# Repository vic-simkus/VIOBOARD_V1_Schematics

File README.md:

# VIOBOARD_V1_Schematics
Schematics for VIOBOAD Version 1.0

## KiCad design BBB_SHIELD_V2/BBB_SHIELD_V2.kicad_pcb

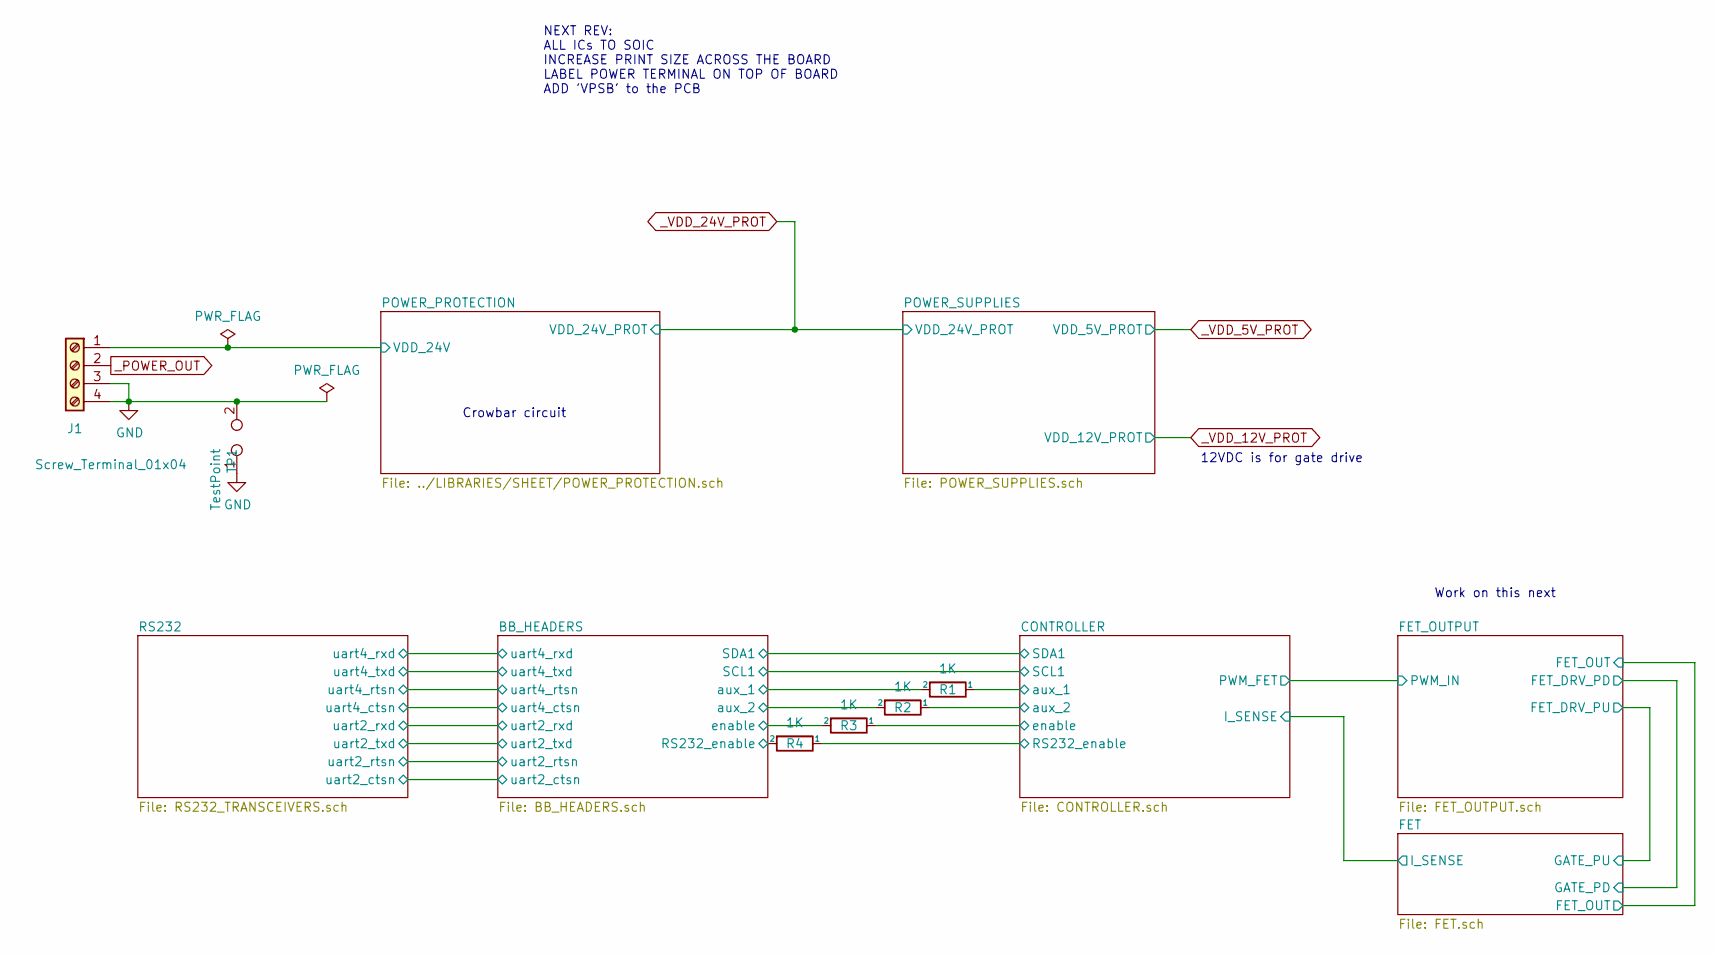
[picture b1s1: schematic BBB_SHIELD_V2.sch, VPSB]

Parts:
J1: Screw_Terminal_01x04; OSTTA044163
R1, R2, R3, R4: 1K; R_0805_2012Metric; MFGPN CRCW08051K00FKEAC
TP1: TestPoint; PinHeader_1x02_P1.27mm_Vertical

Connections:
/BB_HEADERS/RS232_enable: R4.2; also elsewhere on the board
/BB_HEADERS/aux_1: R1.2; also elsewhere on the board
/BB_HEADERS/aux_2: R2.2; also elsewhere on the board
/BB_HEADERS/enable: R3.2; also elsewhere on the board
/CONTROLLER/RS232_enable: R4.1; also elsewhere on the board
/CONTROLLER/aux_1: R1.1; also elsewhere on the board
/CONTROLLER/aux_2: R2.1; also elsewhere on the board
/CONTROLLER/enable: R3.1; also elsewhere on the board
/POWER_PROTECTION/VDD_24V: J1.1; also elsewhere on the board
GND: J1.3, J1.4, TP1.1, TP1.2; also elsewhere on the board
_POWER_OUT: J1.2; also elsewhere on the board

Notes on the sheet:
NEXT REV: ALL ICs TO SOIC INCREASE PRINT SIZE ACROSS THE BOARD LABEL POWER TERMINAL ON TOP OF BOARD ADD 'VPSB' to the PCB
12VDC is for gate drive
Crowbar circuit
Work on this next

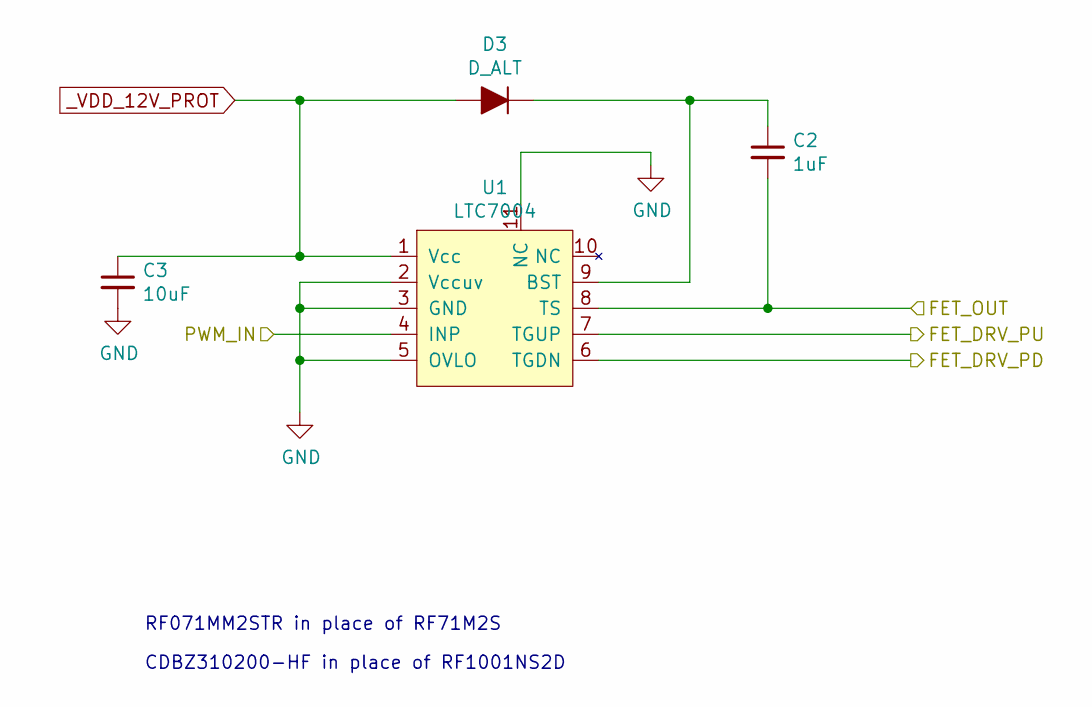
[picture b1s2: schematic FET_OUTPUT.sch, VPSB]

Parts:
C2: 1uF; C_0805_2012Metric; VOLTAGE 50; MFGPN CL21B104KBCNNNC
C3: 10uF; C_1206_3216Metric; VOLTAGE 50; MFGPN CL31B106KBHNNNE
D3: D_ALT; D_SOD-123F; MFGPN RF071MM2STR
U1: LTC7004; MSOP-10; MFGPN LTC7004IMSE#PBF

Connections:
/CONTROLLER/PWM_FET: U1.4 (INP); also elsewhere on the board
/FET/FET_OUT: C2.2, U1.8 (TS); also elsewhere on the board
/FET_OUTPUT/FET_DRV_PD: U1.6 (TGDN); also elsewhere on the board
/FET_OUTPUT/FET_DRV_PU: U1.7 (TGUP); also elsewhere on the board
GND: C3.2, U1.2 (Vccuv), U1.3 (GND), U1.5 (OVLO), U1.11 (NC); also elsewhere on the board
unnamed: C2.1, D3.1 (K), U1.9 (BST)
_VDD_12V_PROT: C3.1, D3.2 (A), U1.1 (Vcc); also elsewhere on the board

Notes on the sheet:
‎RF071MM2STR‎ in place of RF71M2S
CDBZ310200-HF in place of RF1001NS2D

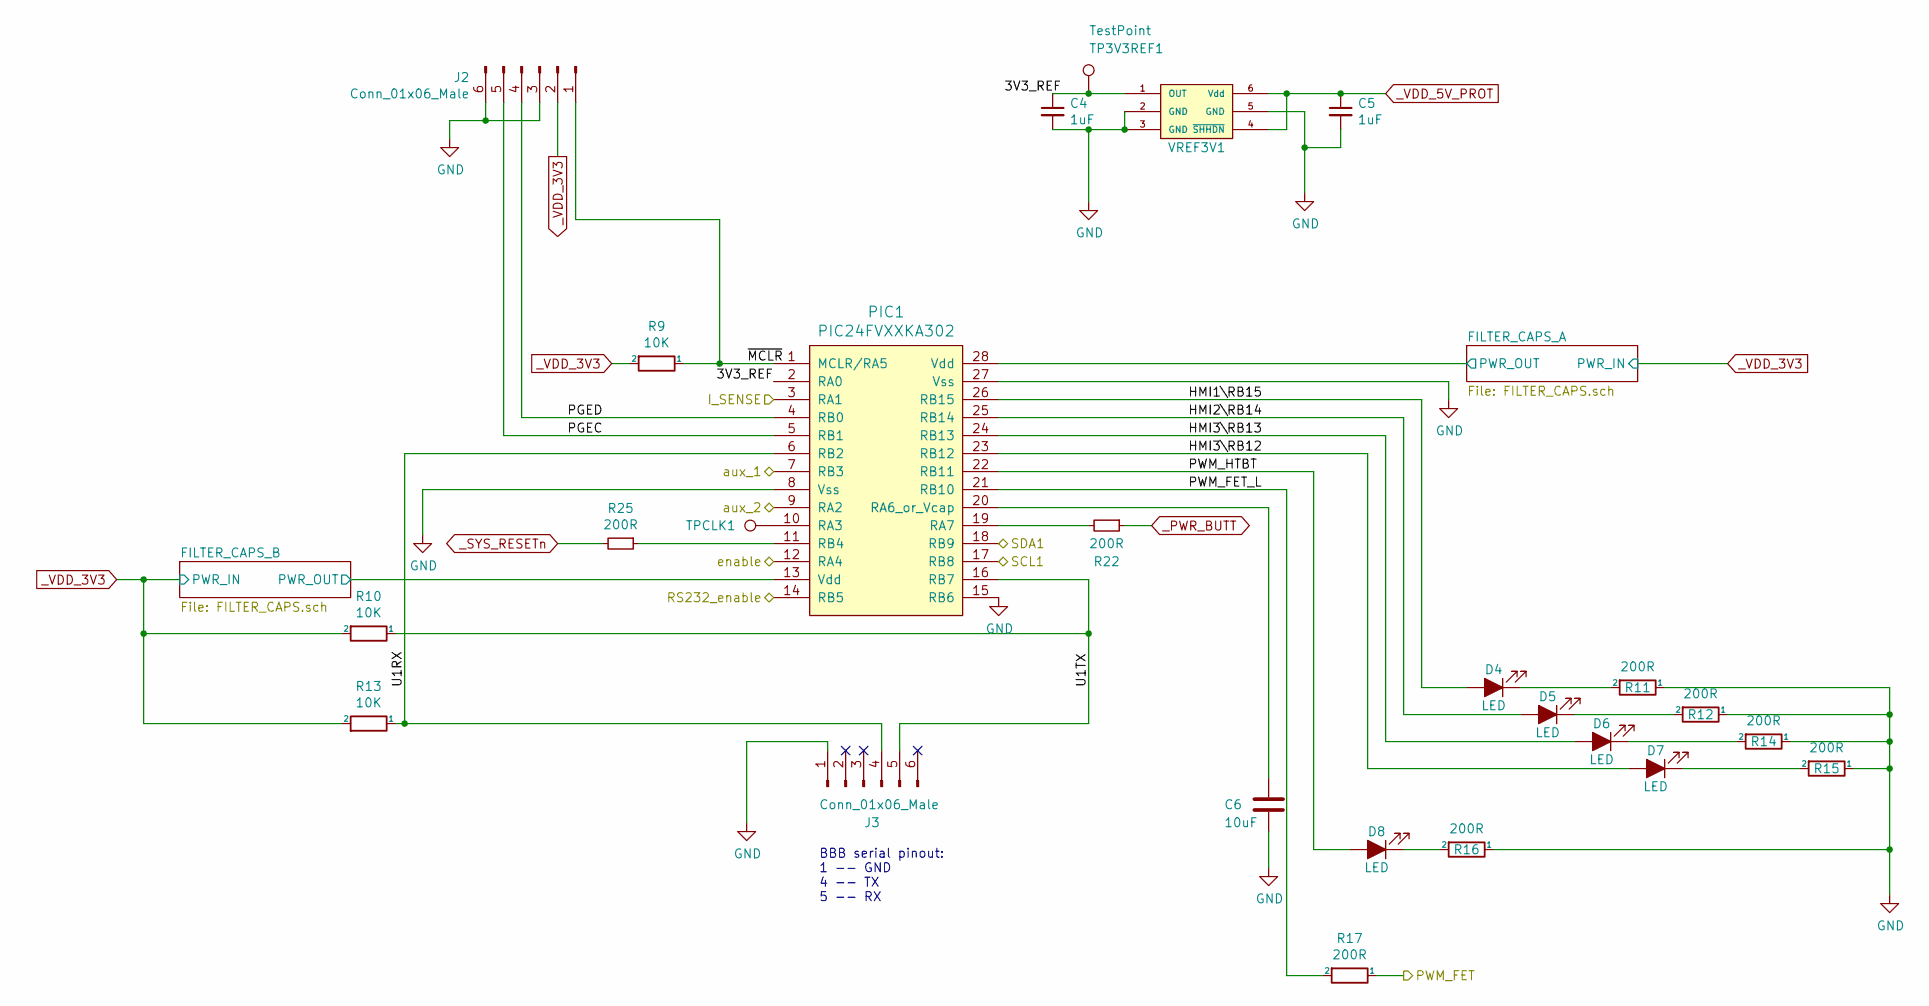
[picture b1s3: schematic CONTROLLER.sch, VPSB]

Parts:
C4, C5: 1uF; C_0805_2012Metric; VOLTAGE 50; MFGPN CL21B105KBFNFNE
C6: 10uF; C_0805_2012Metric; VOLTAGE 10; MFGPN CL21A106KPFNNNE
D4, D5, D6, D7, D8: LED; LED_0805_2012Metric_Castellated; VOLTAGE NA
J2, J3: Conn_01x06_Male; PinHeader_1x06_P2.54mm_Horizontal; MFGPN 0022052061
PIC1: PIC24FVXXKA302; SOIC-28W_7.5x17.9mm_P1.27mm; MFGPN PIC24FV32KA302-I/SO
R9, R10, R13: 10K; R_0805_2012Metric; MFGPN CRCW080510K0FKTA
R11, R12, R14, R15, R16, R17, R22, R25: 200R; R_0805_2012Metric; MFGPN CRCW0805200RFKEAC
TP3V3REF1: TestPoint; TestPoint_THTPad_D1.0mm_Drill0.5mm
TPCLK1: TestPoint; TestPoint_THTPad_D1.0mm_Drill0.5mm
VREF3V1: MCP1501_SOT-23-6; SOT-23-6; MFGPN MCP1501T-33E/CHY

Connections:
/BB_HEADERS/SCL1: PIC1.17 (RB8); also elsewhere on the board
/BB_HEADERS/SDA1: PIC1.18 (RB9); also elsewhere on the board
/CONTROLLER/3V3_REF: C4.1, PIC1.2 (RA0), TP3V3REF1.1, VREF3V1.1 (OUT)
/CONTROLLER/HMI1\RB15: D4.2 (A), PIC1.26 (RB15)
/CONTROLLER/HMI2\RB14: D5.2 (A), PIC1.25 (RB14)
/CONTROLLER/HMI3\RB12: D7.2 (A), PIC1.23 (RB12)
/CONTROLLER/HMI3\RB13: D6.2 (A), PIC1.24 (RB13)
/CONTROLLER/I_SENSE: PIC1.3 (RA1); also elsewhere on the board
/CONTROLLER/PGEC: J2.5, PIC1.5 (RB1)
/CONTROLLER/PGED: J2.4, PIC1.4 (RB0)
/CONTROLLER/PWM_FET: R17.1; also elsewhere on the board
/CONTROLLER/PWM_FET_L: PIC1.21 (RB10), R17.2
/CONTROLLER/PWM_HTBT: D8.2 (A), PIC1.22 (RB11)
/CONTROLLER/RS232_enable: PIC1.14 (RB5); also elsewhere on the board
/CONTROLLER/U1RX: J3.4, PIC1.6 (RB2), R13.1
/CONTROLLER/U1TX: J3.5, PIC1.16 (RB7), R10.1
/CONTROLLER/aux_1: PIC1.7 (RB3); also elsewhere on the board
/CONTROLLER/aux_2: PIC1.9 (RA2); also elsewhere on the board
/CONTROLLER/enable: PIC1.12 (RA4); also elsewhere on the board
/CONTROLLER/~MCLR: J2.1, PIC1.1 (MCLR/RA5), R9.1
GND: C4.2, C5.2, C6.2, J2.3, J2.6, J3.1, PIC1.8 (Vss), PIC1.15 (RB6), PIC1.27 (Vss), R11.1, R12.1, R14.1, R15.1, R16.1, VREF3V1.2 (GND), VREF3V1.3 (GND), VREF3V1.5 (GND); also elsewhere on the board
unnamed: C6.1, PIC1.20 (RA6_or_Vcap)
unnamed: D4.1 (K), R11.2
unnamed: D5.1 (K), R12.2
unnamed: D6.1 (K), R14.2
unnamed: D7.1 (K), R15.2
unnamed: D8.1 (K), R16.2
unnamed: PIC1.10 (RA3), TPCLK1.1
unnamed: PIC1.11 (RB4), R25.1
unnamed: PIC1.19 (RA7), R22.2
_PWR_BUTT: R22.1; also elsewhere on the board
_SYS_RESETn: R25.2; also elsewhere on the board
_VDD_3V3: J2.2, PIC1.13 (Vdd), PIC1.28 (Vdd), R9.2, R10.2, R13.2; also elsewhere on the board
_VDD_5V_PROT: C5.1, VREF3V1.4 (~SHHDN), VREF3V1.6 (Vdd); also elsewhere on the board

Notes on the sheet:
BBB serial pinout: 1 -- GND 4 -- TX 5 -- RX

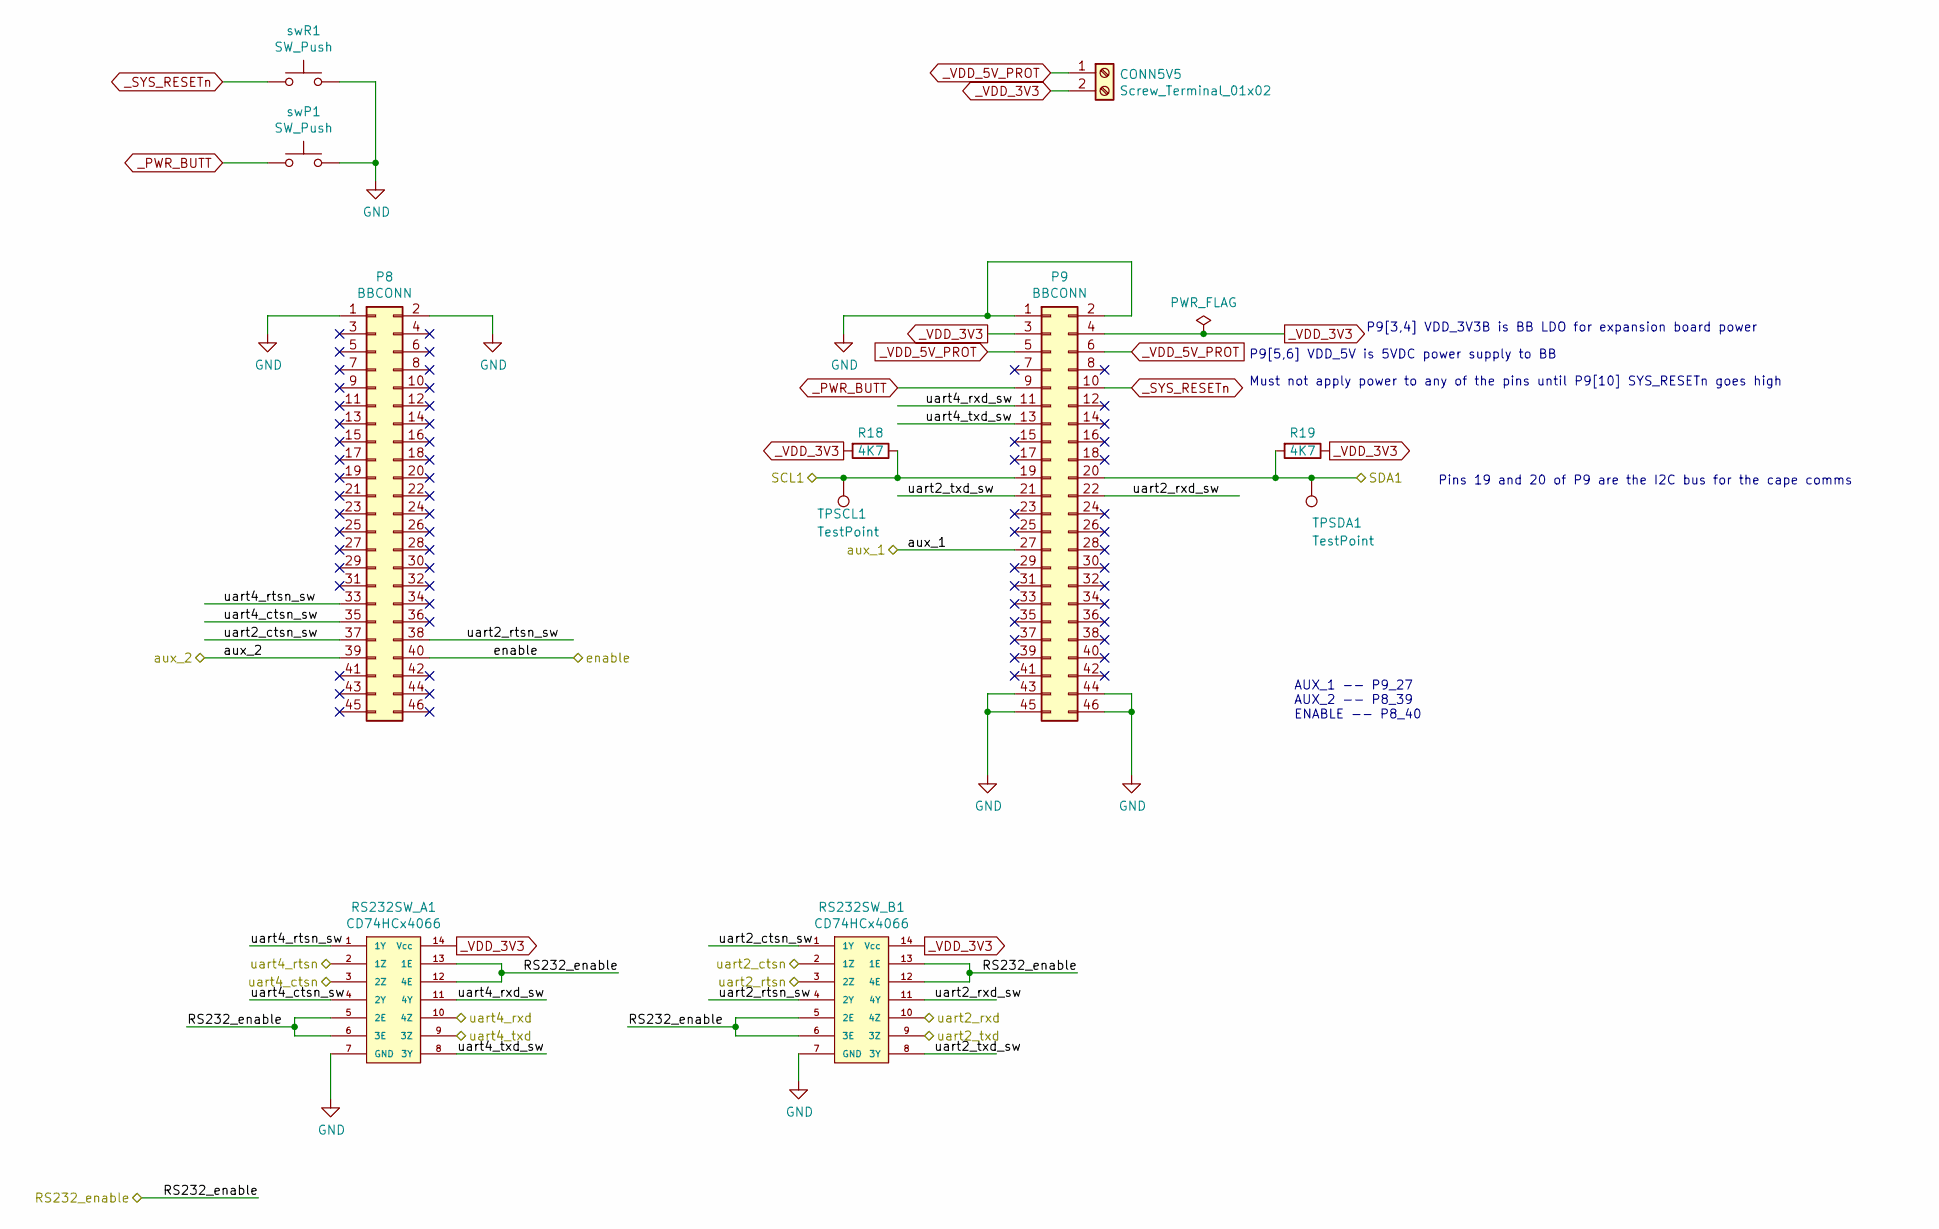
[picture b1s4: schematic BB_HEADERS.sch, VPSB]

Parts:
CONN5V5: Screw_Terminal_01x02; OSTTA024163
P8, P9: BBCONN; PinHeader_2x23_P2.54mm_Vertical
R18, R19: 4K7; R_0805_2012Metric; MFGPN CRCW08054K70FKEAC
RS232SW_A1, RS232SW_B1: CD74HCx4066; SOIC-14_3.9x8.7mm_P1.27mm; MFGPN CD74HC4066M96
TPSCL1: TestPoint; PinHeader_1x01_P1.27mm_Vertical
TPSDA1: TestPoint; PinHeader_1x01_P1.27mm_Vertical
swP1: SW_Push; SW_PUSH_6mm
swR1: SW_Push; SW_PUSH_6mm

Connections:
/BB_HEADERS/RS232_enable: RS232SW_A1.5 (2E), RS232SW_A1.6 (3E), RS232SW_A1.12 (4E), RS232SW_A1.13 (1E), RS232SW_B1.5 (2E), RS232SW_B1.6 (3E), RS232SW_B1.12 (4E), RS232SW_B1.13 (1E); also elsewhere on the board
/BB_HEADERS/SCL1: P9.19, R18.1, TPSCL1.1; also elsewhere on the board
/BB_HEADERS/SDA1: P9.20, R19.2, TPSDA1.1; also elsewhere on the board
/BB_HEADERS/aux_1: P9.27; also elsewhere on the board
/BB_HEADERS/aux_2: P8.39; also elsewhere on the board
/BB_HEADERS/enable: P8.40; also elsewhere on the board
/BB_HEADERS/uart2_ctsn: RS232SW_B1.2 (1Z); also elsewhere on the board
/BB_HEADERS/uart2_ctsn_sw: P8.37, RS232SW_B1.1 (1Y)
/BB_HEADERS/uart2_rtsn: RS232SW_B1.3 (2Z); also elsewhere on the board
/BB_HEADERS/uart2_rtsn_sw: P8.38, RS232SW_B1.4 (2Y)
/BB_HEADERS/uart2_rxd: RS232SW_B1.10 (4Z); also elsewhere on the board
/BB_HEADERS/uart2_rxd_sw: P9.22, RS232SW_B1.11 (4Y)
/BB_HEADERS/uart2_txd: RS232SW_B1.9 (3Z); also elsewhere on the board
/BB_HEADERS/uart2_txd_sw: P9.21, RS232SW_B1.8 (3Y)
/BB_HEADERS/uart4_ctsn: RS232SW_A1.3 (2Z); also elsewhere on the board
/BB_HEADERS/uart4_ctsn_sw: P8.35, RS232SW_A1.4 (2Y)
/BB_HEADERS/uart4_rtsn: RS232SW_A1.2 (1Z); also elsewhere on the board
/BB_HEADERS/uart4_rtsn_sw: P8.33, RS232SW_A1.1 (1Y)
/BB_HEADERS/uart4_rxd: RS232SW_A1.10 (4Z); also elsewhere on the board
/BB_HEADERS/uart4_rxd_sw: P9.11, RS232SW_A1.11 (4Y)
/BB_HEADERS/uart4_txd: RS232SW_A1.9 (3Z); also elsewhere on the board
/BB_HEADERS/uart4_txd_sw: P9.13, RS232SW_A1.8 (3Y)
GND: P8.1, P8.2, P9.1, P9.2, P9.43, P9.44, P9.45, P9.46, RS232SW_A1.7 (GND), RS232SW_B1.7 (GND), swP1.2, swR1.2; also elsewhere on the board
_PWR_BUTT: P9.9, swP1.1; also elsewhere on the board
_SYS_RESETn: P9.10, swR1.1; also elsewhere on the board
_VDD_3V3: CONN5V5.2, P9.3, P9.4, R18.2, R19.1, RS232SW_A1.14 (Vcc), RS232SW_B1.14 (Vcc); also elsewhere on the board
_VDD_5V_PROT: CONN5V5.1, P9.5, P9.6; also elsewhere on the board

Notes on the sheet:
P9[3,4] VDD_3V3B is BB LDO for expansion board power
P9[5,6] VDD_5V is 5VDC power supply to BB
Must not apply power to any of the pins until P9[10] SYS_RESETn goes high
Pins 19 and 20 of P9 are the I2C bus for the cape comms
AUX_1 -- P9_27 AUX_2 -- P8_39 ENABLE -- P8_40

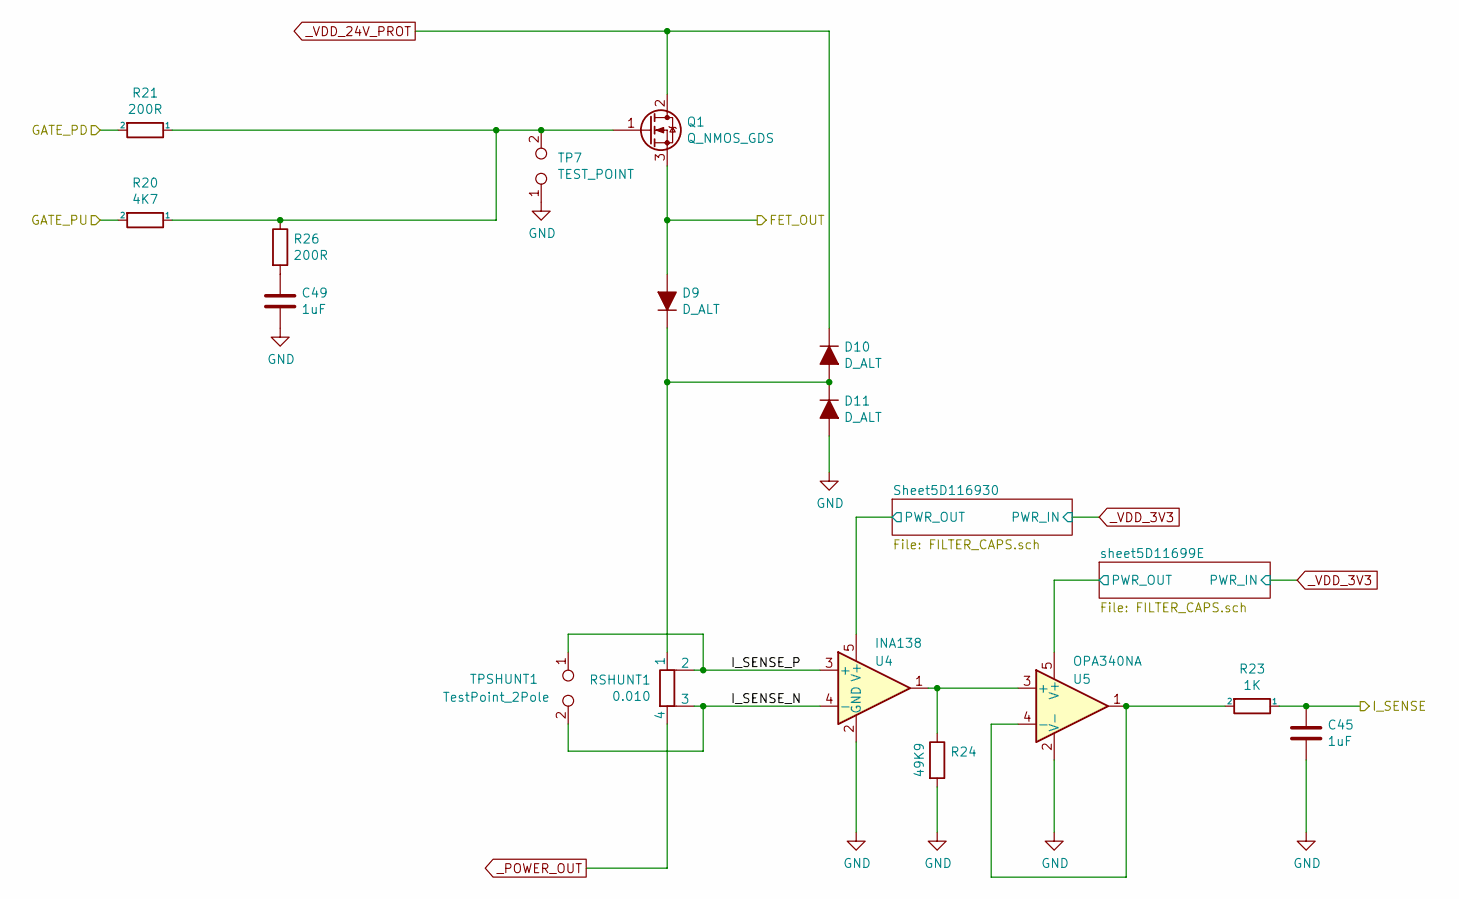
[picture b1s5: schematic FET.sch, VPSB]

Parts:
C45: 1uF; C_0805_2012Metric; VOLTAGE 50; MFGPN CL31A225KB9LNNC
C49: 1uF; C_0805_2012Metric
D9, D10, D11: D_ALT; COMCHIP_TO_277; MFGPN CDBZ310200-HF
Q1: Q_NMOS_GDS; TO-220-3_Vertical; MFGPN PHP29N08T,127
R20: 4K7; R_0805_2012Metric; MFGPN ERJ-P06F1000V
R21, R26: 200R; R_0805_2012Metric; MFGPN CRCW0805200RFKEAC
R23: 1K; R_0805_2012Metric; MFGPN CRCW08051K00FKEAC
R24: 49K9; R_0805_2012Metric; MFGPN CRCW080549K9DHEAP
RSHUNT1: 0.010; 1206_WIDE_SHUNT; MFGPN CFG0612-FX-R010ELF
TP7: TEST_POINT; PinHeader_1x02_P1.27mm_Vertical; MFGPN M50-3530242
TPSHUNT1: TestPoint_2Pole; PinHeader_1x02_P1.27mm_Vertical
U4: INA138; SOT-23-5; MFGPN INA138NA/3K
U5: OPA340NA; SOT-23-5; MFGPN OPA340NA/3K

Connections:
/CONTROLLER/I_SENSE: C45.1, R23.1; also elsewhere on the board
/FET/FET_OUT: D9.2 (A), Q1.3 (S); also elsewhere on the board
/FET/I_SENSE_N: RSHUNT1.3, TPSHUNT1.2, U4.4 (-)
/FET/I_SENSE_P: RSHUNT1.2, TPSHUNT1.1, U4.3 (+)
/FET_OUTPUT/FET_DRV_PD: R21.2; also elsewhere on the board
/FET_OUTPUT/FET_DRV_PU: R20.2; also elsewhere on the board
GND: C45.2, C49.2, D11.2 (A), R24.2, TP7.1, U4.2 (GND), U5.2 (V-); also elsewhere on the board
unnamed: C49.1, R26.2
unnamed: D9.1 (K), D10.2 (A), D11.1 (K), RSHUNT1.1
unnamed: Q1.1 (G), R20.1, R21.1, R26.1, TP7.2
unnamed: R23.2, U5.1, U5.4 (-)
unnamed: R24.1, U4.1, U5.3 (+)
_POWER_OUT: RSHUNT1.4; also elsewhere on the board
_VDD_3V3: U4.5 (V+), U5.5 (V+); also elsewhere on the board
_VDD_24V_PROT: D10.1 (K), Q1.2 (D); also elsewhere on the board

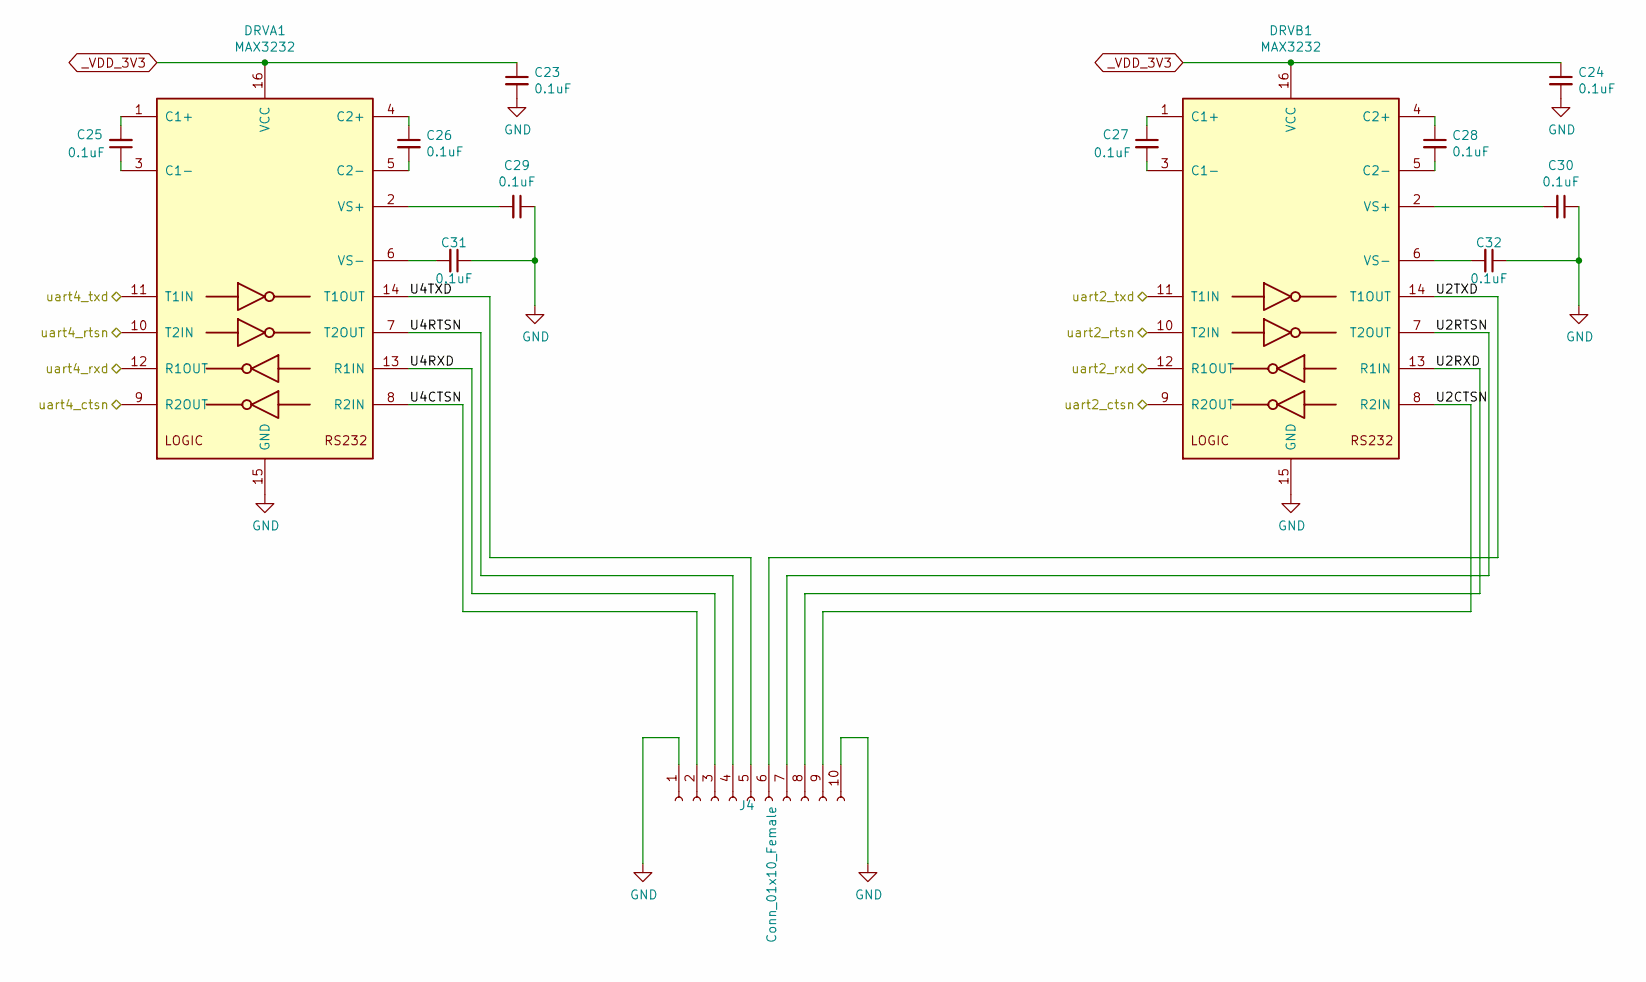
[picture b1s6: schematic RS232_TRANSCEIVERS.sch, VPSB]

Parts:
C23, C24, C25, C26, C27, C28, C29, C30, C31, C32: 0.1uF; C_0805_2012Metric; VOLTAGE 50; MFGPN CL21B104KBCNNNC
DRVA1: MAX3232; SOIC-16_3.9x9.9mm_P1.27mm; MFGPN MAX3232ECDR
DRVB1: MAX3232; SOIC-16_3.9x9.9mm_P1.27mm; MFGPN MAX3232ECDR
J4: Conn_01x10_Female; 10_POS_SPRING_TERM

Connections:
/BB_HEADERS/uart2_ctsn: DRVB1.9 (R2OUT); also elsewhere on the board
/BB_HEADERS/uart2_rtsn: DRVB1.10 (T2IN); also elsewhere on the board
/BB_HEADERS/uart2_rxd: DRVB1.12 (R1OUT); also elsewhere on the board
/BB_HEADERS/uart2_txd: DRVB1.11 (T1IN); also elsewhere on the board
/BB_HEADERS/uart4_ctsn: DRVA1.9 (R2OUT); also elsewhere on the board
/BB_HEADERS/uart4_rtsn: DRVA1.10 (T2IN); also elsewhere on the board
/BB_HEADERS/uart4_rxd: DRVA1.12 (R1OUT); also elsewhere on the board
/BB_HEADERS/uart4_txd: DRVA1.11 (T1IN); also elsewhere on the board
/RS232/U2CTSN: DRVB1.8 (R2IN), J4.9
/RS232/U2RTSN: DRVB1.7 (T2OUT), J4.7
/RS232/U2RXD: DRVB1.13 (R1IN), J4.8
/RS232/U2TXD: DRVB1.14 (T1OUT), J4.6
/RS232/U4CTSN: DRVA1.8 (R2IN), J4.2
/RS232/U4RTSN: DRVA1.7 (T2OUT), J4.4
/RS232/U4RXD: DRVA1.13 (R1IN), J4.3
/RS232/U4TXD: DRVA1.14 (T1OUT), J4.5
GND: C23.2, C24.2, C29.1, C30.1, C31.1, C32.1, DRVA1.15 (GND), DRVB1.15 (GND), J4.1, J4.10; also elsewhere on the board
unnamed: C25.1, DRVA1.3 (C1-)
unnamed: C25.2, DRVA1.1 (C1+)
unnamed: C26.1, DRVA1.4 (C2+)
unnamed: C26.2, DRVA1.5 (C2-)
unnamed: C27.1, DRVB1.1 (C1+)
unnamed: C27.2, DRVB1.3 (C1-)
unnamed: C28.1, DRVB1.4 (C2+)
unnamed: C28.2, DRVB1.5 (C2-)
unnamed: C29.2, DRVA1.2 (VS+)
unnamed: C30.2, DRVB1.2 (VS+)
unnamed: C31.2, DRVA1.6 (VS-)
unnamed: C32.2, DRVB1.6 (VS-)
_VDD_3V3: C23.1, C24.1, DRVA1.16 (VCC), DRVB1.16 (VCC); also elsewhere on the board

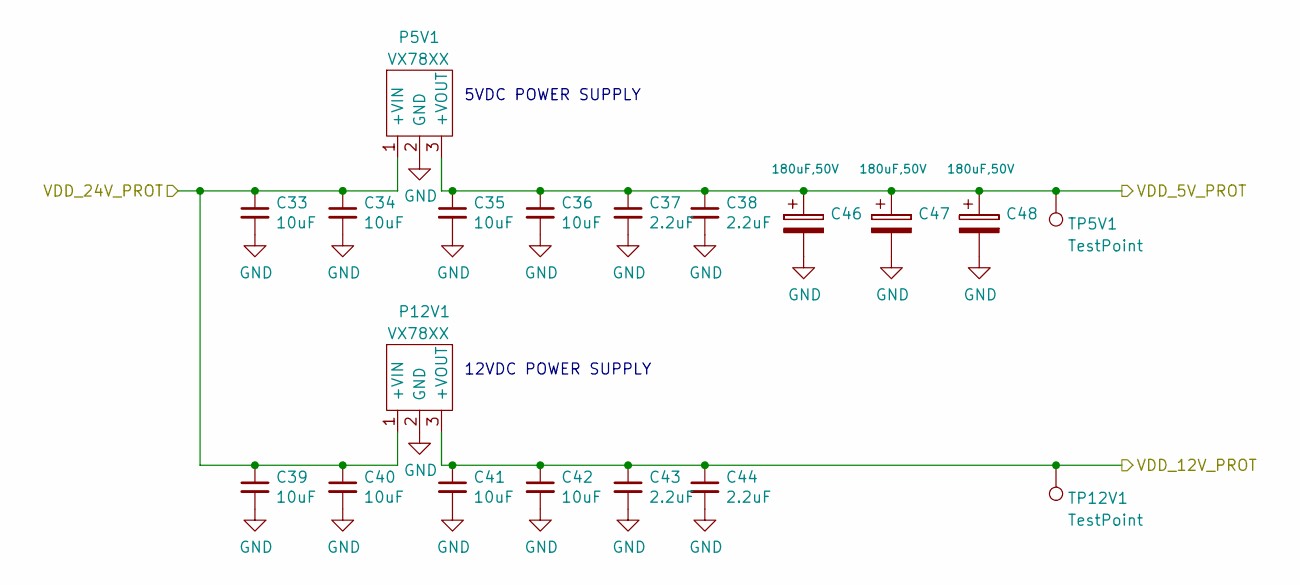
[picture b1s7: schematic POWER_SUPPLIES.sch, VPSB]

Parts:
C33, C34, C35, C36, C39, C40, C41, C42: 10uF; C_1206_3216Metric; VOLTAGE 50; MFGPN CL31B106KBHNNNE
C37, C38, C43, C44: 2.2uF; C_1206_3216Metric; VOLTAGE 50; MFGPN CL31A225KB9LNNC
C46, C47, C48: 180uF,50V; CP_Radial_D8.0mm_P3.50mm; MFGPN UPW1H181MPD
P5V1: VX78XX; Vx78-1000; MFGPN VX78012-1000
P12V1: VX78XX; Vx78-1000; MFGPN VX7805-1000
TP5V1, TP12V1: TestPoint; TestPoint_THTPad_D1.0mm_Drill0.5mm

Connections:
GND: C33.2, C34.2, C35.2, C36.2, C37.2, C38.2, C39.2, C40.2, C41.2, C42.2, C43.2, C44.2, C46.2, C47.2, C48.2, P5V1.2 (GND), P12V1.2 (GND); also elsewhere on the board
_VDD_5V_PROT: C35.1, C36.1, C37.1, C38.1, C46.1, C47.1, C48.1, P5V1.3 (+VOUT), TP5V1.1; also elsewhere on the board
_VDD_12V_PROT: C41.1, C42.1, C43.1, C44.1, P12V1.3 (+VOUT), TP12V1.1; also elsewhere on the board
_VDD_24V_PROT: C33.1, C34.1, C39.1, C40.1, P5V1.1 (+VIN), P12V1.1 (+VIN); also elsewhere on the board

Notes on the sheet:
5VDC POWER SUPPLY
12VDC POWER SUPPLY

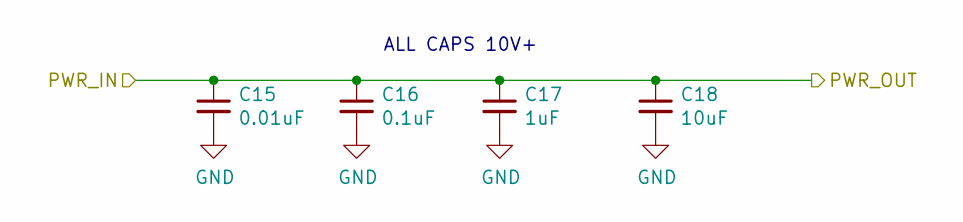
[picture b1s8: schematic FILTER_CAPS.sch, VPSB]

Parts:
C7: 0.01uF; C_0805_2012Metric; VOLTAGE 50; MFGPN CL21B103KBANNNC
C8: 0.1uF; C_0805_2012Metric; VOLTAGE 50; MFGPN CL21B104KBCNNNC
C9: 1uF; C_0805_2012Metric; VOLTAGE 50; MFGPN CL21B105KBFNFNE
C10: 10uF; C_0805_2012Metric; VOLTAGE 10; MFGPN CL21A106KPFNNNE

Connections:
GND: C7.2, C8.2, C9.2, C10.2; also elsewhere on the board
_VDD_3V3: C7.1, C8.1, C9.1, C10.1; also elsewhere on the board

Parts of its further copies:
C11, C15, C19: 0.01uF; C_0805_2012Metric; VOLTAGE 50; MFGPN CL21B103KBANNNC
C12, C16, C20: 0.1uF; C_0805_2012Metric; VOLTAGE 50; MFGPN CL21B104KBCNNNC
C13, C17, C21: 1uF; C_0805_2012Metric; VOLTAGE 50; MFGPN CL21B105KBFNFNE
C14, C18, C22: 10uF; C_0805_2012Metric; VOLTAGE 10; MFGPN CL21A106KPFNNNE

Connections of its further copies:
GND: C11.2, C12.2, C13.2, C14.2, C15.2, C16.2, C17.2, C18.2, C19.2, C20.2, C21.2, C22.2; also elsewhere on the board
_VDD_3V3: C11.1, C12.1, C13.1, C14.1, C15.1, C16.1, C17.1, C18.1, C19.1, C20.1, C21.1, C22.1; also elsewhere on the board

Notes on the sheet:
ALL CAPS 10V+

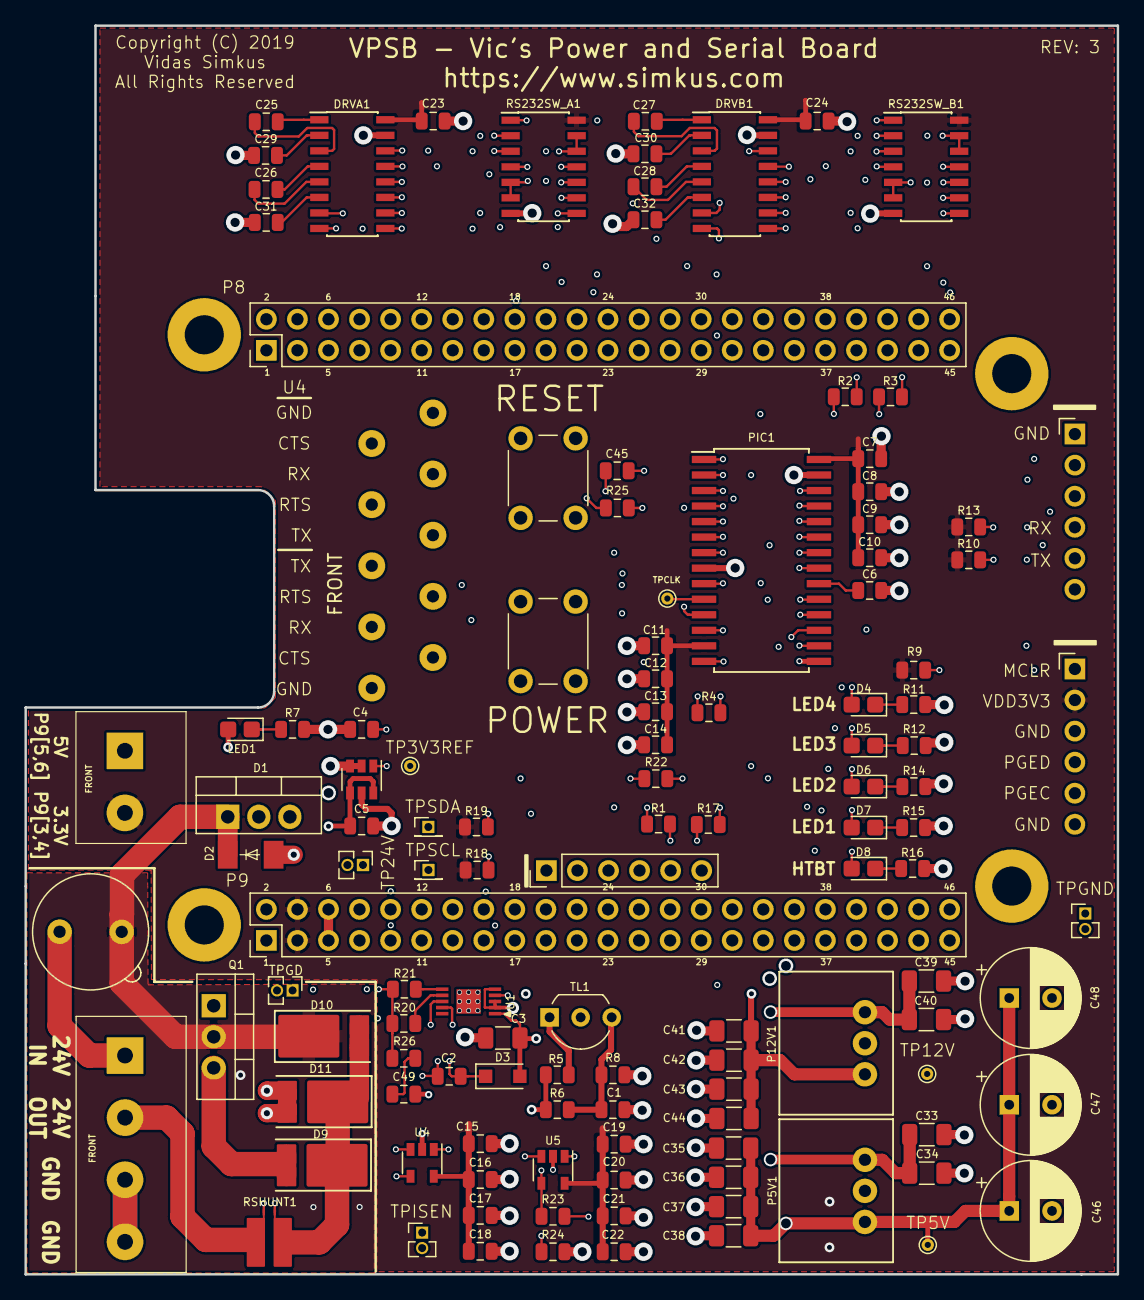
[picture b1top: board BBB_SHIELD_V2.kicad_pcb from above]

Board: 4 copper layers, 89.3 x 102.1 mm, 121 parts (0 on the bottom side), 92 nets.

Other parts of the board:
C1: 0.1uF; C_0805_2012Metric
D1: 24V_TRIAC; TO-220-3_Vertical
D2: D_ALT; DO-214AA
F1: 24V_IN; Fuseholder_TR5_Littelfuse_No560_No460
LED1: LED; LED_0805_2012Metric_Castellated
R5: 1K; R_0805_2012Metric
R6: 49K9; R_0805_2012Metric
R7, R8: 4K7; R_0805_2012Metric
TL1: 24V_REF; TO-92_Inline_Wide_TI
TP2: TEST_POINT; PinHeader_1x02_P1.27mm_Vertical

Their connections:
/POWER_PROTECTION/VDD_24V: F1.1; also elsewhere on the board
/POWER_PROTECTION/VDD_24V_SHUNT: D1.3, R5.2, TL1.1
GND: C1.2, D1.2, D2.2, R7.2, R8.2, TL1.2, TP2.1; also elsewhere on the board
unnamed: C1.1, R6.2, R8.1, TL1.3
unnamed: LED1.1, R7.1
_VDD_24V_PROT: D1.1, D2.1, F1.2, LED1.2, R5.1, R6.1, TP2.2; also elsewhere on the board

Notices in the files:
BBB_SHIELD/BBB_SHIELD.kicad_pcb:
Copyright (c) 2017 Vidas Simkus
All rights reserved
BBB_SHIELD_V2/BBB_SHIELD_V2.kicad_pcb:
Copyright (C) 2019
BBB_SHIELD_V2/BBB_SHIELD_V2.sch:
Copyright (C) 2019 Vidas Simkus
VIOBOARD/5V_POWER_SUPPLY.sch:
Copyright Vidas Simkus 2018
Licensed under CERN OHL v.1.2
VIOBOARD/VIOBOARD.kicad_pcb:
Copyright 2018 Vidas Simkus
Copyright (c) 2018 Vidas Simkus
